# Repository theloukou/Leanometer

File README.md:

# Leanometer - IN DEVELOPMENT
ESP32-based motorcycle leanometer

This is version 2 of my open-source motorcycle leanometer, based on ESP32 SoM, programmed on Arduino.
Designed mainly to be compact, low cost, and easy to assemble with household equipment/average soldering skills.

3D printed enclosure has been tested to be water resistant over 12 hour water exposure. Additional weather proofing can be achieved by using some kind of conformal coating on electronics (i.e. Kontakt Plastik 70).

Additional parts needed are:
1.  **GY-521 MPU-6050** IMU module  ???
2. 26.5mm x 29mm x 3mm Plexiglass piece  ???
3. 6 pieces of M2.5x5mm bolts  ???
4. some kind of 2 component adhesive/thermoglue  ???

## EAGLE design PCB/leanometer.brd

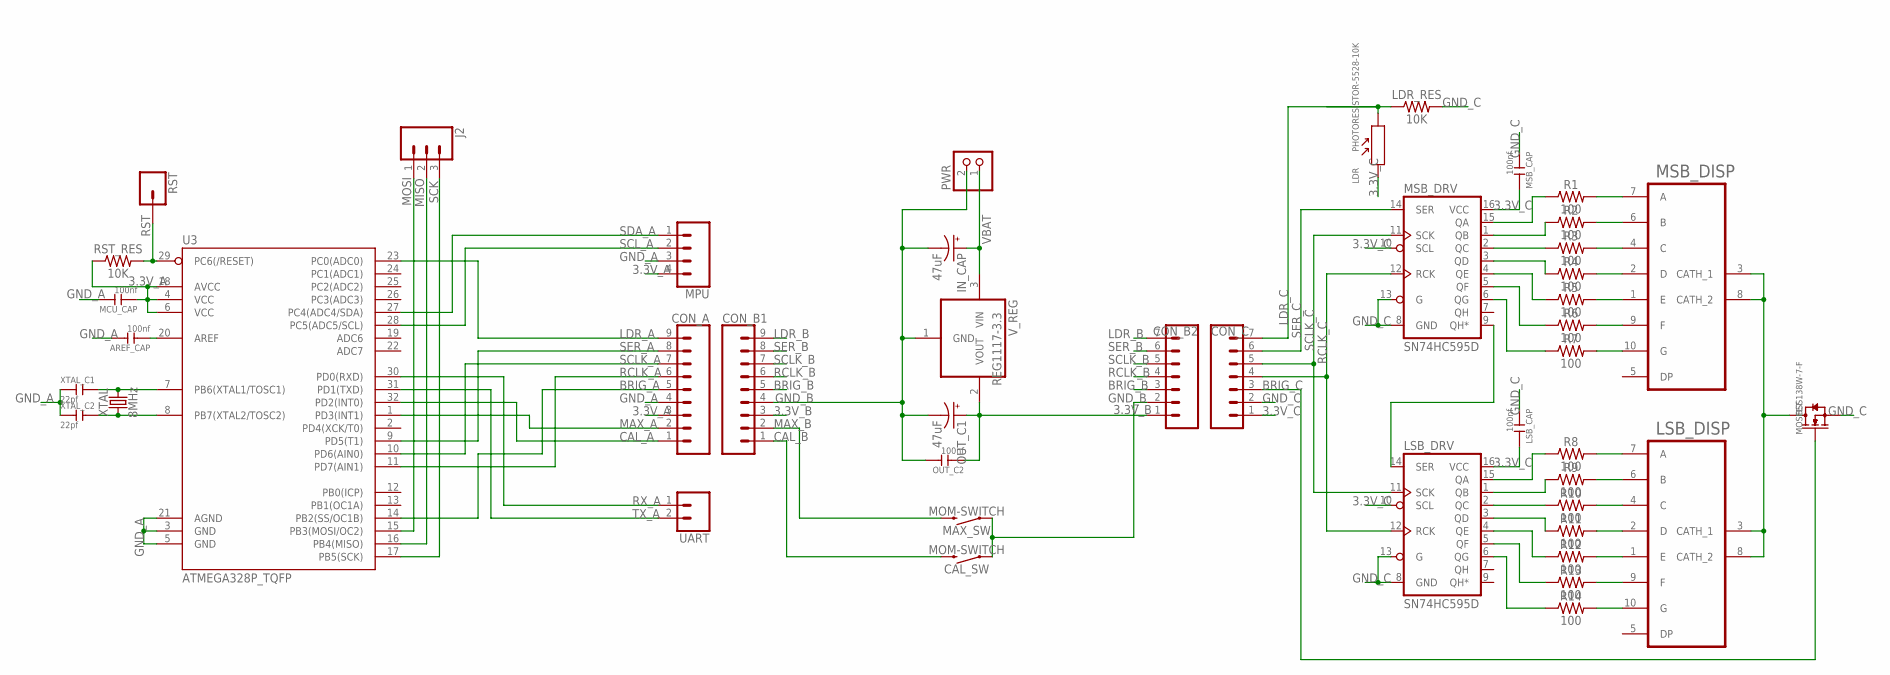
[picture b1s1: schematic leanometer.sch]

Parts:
AREF_CAP: 100nf; C0805
CAL_SW: MOM-SWITCH; TACTILE_SWITCH_PTH_6.0MM
CON_A: CONN_09; 1X09
CON_B1: CONN_09; 1X09
CON_B2: CONN_07; 1X07
CON_C: CONN_07; 1X07
IN_CAP: 47uF; CPOL-RADIAL-2.5MM-6.5MM
J2: CONN_03; 1X03
LDR: PHOTORESISTOR-5528-10K; SNR2-3.0
LDR_RES: 10K; 0805
LSB_CAP: 100nf; C0805
LSB_DISP: OPD-S5621LE-BW; 0.56''_LED_DISPLAY
LSB_DRV: SN74HC595D; SO16
MAX_SW: MOM-SWITCH; TACTILE_SWITCH_PTH_6.0MM
MCU_CAP: 100nf; C0805
MOSFET: BSS138W-7-F; SOT-23
MPU: CONN_04; 1X04
MSB_CAP: 100nf; C0805
MSB_DISP: OPD-S5621LE-BW; 0.56''_LED_DISPLAY
MSB_DRV: SN74HC595D; SO16
OUT_C1: 47uF; CPOL-RADIAL-2.5MM-6.5MM
OUT_C2: 100nf; C0805
PWR: JST_2PIN-THM-RA; JST-PH-2-THM-RA
R1, R2, R3, R4, R5, R6, R7, R8, R9, R10, R11, R12, R13, R14: 100; 0805
RST: CONN_01; 1X01
RST_RES: 10K; 0805
U3: ATMEGA328P_TQFP; TQFP32-08
UART: CONN_02; 1X02
V_REG: REG1117-3.3; SOT223
XTAL: 8MHz; HC49US
XTAL_C1, XTAL_C2: 22pf; C0805

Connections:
3.3V_A: CON_A.3, MCU_CAP.1, MPU.4, RST_RES.1, U3.4 (VCC), U3.6 (VCC), U3.18 (AVCC)
3.3V_B: CON_B1.3, CON_B2.1, OUT_C1.1 (+), OUT_C2.1, V_REG.2 (VOUT)
3.3V_C: CON_C.1, LDR.1, LSB_CAP.2, LSB_DRV.10 (SCL), LSB_DRV.16 (VCC), MSB_CAP.2, MSB_DRV.10 (SCL), MSB_DRV.16 (VCC)
BRIG_A: CON_A.5, U3.14 (PB2(SS/OC1B))
BRIG_B: CON_B1.5, CON_B2.3
BRIG_C: CON_C.3, MOSFET.1 (G)
CAL_A: CON_A.1, U3.32 (PD2(INT0))
CAL_B: CAL_SW.3 (2), CON_B1.1
GND_A: AREF_CAP.2, CON_A.4, MCU_CAP.2, MPU.3, U3.3 (GND), U3.5 (GND), U3.21 (AGND), XTAL_C1.1, XTAL_C2.1
GND_B: CAL_SW.1, CON_B1.4, CON_B2.2, IN_CAP.2 (-), MAX_SW.1, OUT_C1.2 (-), OUT_C2.2, PWR.2 (1), V_REG.1 (GND)
GND_C: CON_C.2, LDR_RES.2, LSB_CAP.1, LSB_DRV.8 (GND), LSB_DRV.13 (G), MOSFET.2 (S), MSB_CAP.1, MSB_DRV.8 (GND), MSB_DRV.13 (G)
LDR_A: CON_A.9, U3.23 (PC0(ADC0))
LDR_B: CON_B1.9, CON_B2.7
LDR_C: CON_C.7, LDR.2, LDR_RES.1
MAX_A: CON_A.2, U3.1 (PD3(INT1))
MAX_B: CON_B1.2, MAX_SW.3 (2)
MISO: J2.2, U3.16 (PB4(MISO))
MOSI: J2.1, U3.15 (PB3(MOSI/OC2))
unnamed: MSB_DISP.7 (A), R1.2
unnamed: MSB_DISP.6 (B), R2.2
unnamed: MSB_DISP.4 (C), R3.2
unnamed: MSB_DISP.2 (D), R4.2
unnamed: MSB_DISP.1 (E), R5.2
unnamed: MSB_DISP.9 (F), R6.2
unnamed: MSB_DISP.10 (G), R7.2
unnamed: LSB_DISP.7 (A), R8.2
unnamed: LSB_DISP.6 (B), R9.2
unnamed: LSB_DISP.4 (C), R10.2
unnamed: LSB_DISP.2 (D), R11.2
unnamed: LSB_DISP.1 (E), R12.2
unnamed: LSB_DISP.9 (F), R13.2
unnamed: LSB_DISP.10 (G), R14.2
unnamed: MSB_DRV.1 (QB), R2.1
unnamed: LSB_DRV.1 (QB), R9.1
unnamed: MSB_DRV.2 (QC), R3.1
unnamed: MSB_DRV.3 (QD), R4.1
unnamed: MSB_DRV.4 (QE), R5.1
unnamed: MSB_DRV.5 (QF), R6.1
unnamed: MSB_DRV.6 (QG), R7.1
unnamed: MSB_DRV.15 (QA), R1.1
unnamed: LSB_DRV.15 (QA), R8.1
unnamed: LSB_DRV.2 (QC), R10.1
unnamed: LSB_DRV.3 (QD), R11.1
unnamed: LSB_DRV.4 (QE), R12.1
unnamed: LSB_DRV.5 (QF), R13.1
unnamed: LSB_DRV.6 (QG), R14.1
unnamed: LSB_DRV.14 (SER), MSB_DRV.9 (QH*)
unnamed: LSB_DISP.3 (CATH_1), LSB_DISP.8 (CATH_2), MOSFET.3 (D), MSB_DISP.3 (CATH_1), MSB_DISP.8 (CATH_2)
unnamed: U3.7 (PB6(XTAL1/TOSC1)), XTAL.2, XTAL_C1.2
unnamed: U3.8 (PB7(XTAL2/TOSC2)), XTAL.1, XTAL_C2.2
unnamed: AREF_CAP.1, U3.20 (AREF)
RCLK_A: CON_A.6, U3.11 (PD7(AIN1))
RCLK_B: CON_B1.6, CON_B2.4
RCLK_C: CON_C.4, LSB_DRV.12 (RCK), MSB_DRV.12 (RCK)
RST: RST.1, RST_RES.2, U3.29 (PC6(/RESET))
RX_A: U3.30 (PD0(RXD)), UART.1
SCK: J2.3, U3.17 (PB5(SCK))
SCLK_A: CON_A.7, U3.10 (PD6(AIN0))
SCLK_B: CON_B1.7, CON_B2.5
SCLK_C: CON_C.5, LSB_DRV.11 (SCK), MSB_DRV.11 (SCK)
SCL_A: MPU.2, U3.28 (PC5(ADC5/SCL))
SDA_A: MPU.1, U3.27 (PC4(ADC4/SDA))
SER_A: CON_A.8, U3.9 (PD5(T1))
SER_B: CON_B1.8, CON_B2.6
SER_C: CON_C.6, MSB_DRV.14 (SER)
TX_A: U3.31 (PD1(TXD)), UART.2
VBAT: IN_CAP.1 (+), PWR.1 (2), V_REG.3 (VIN)

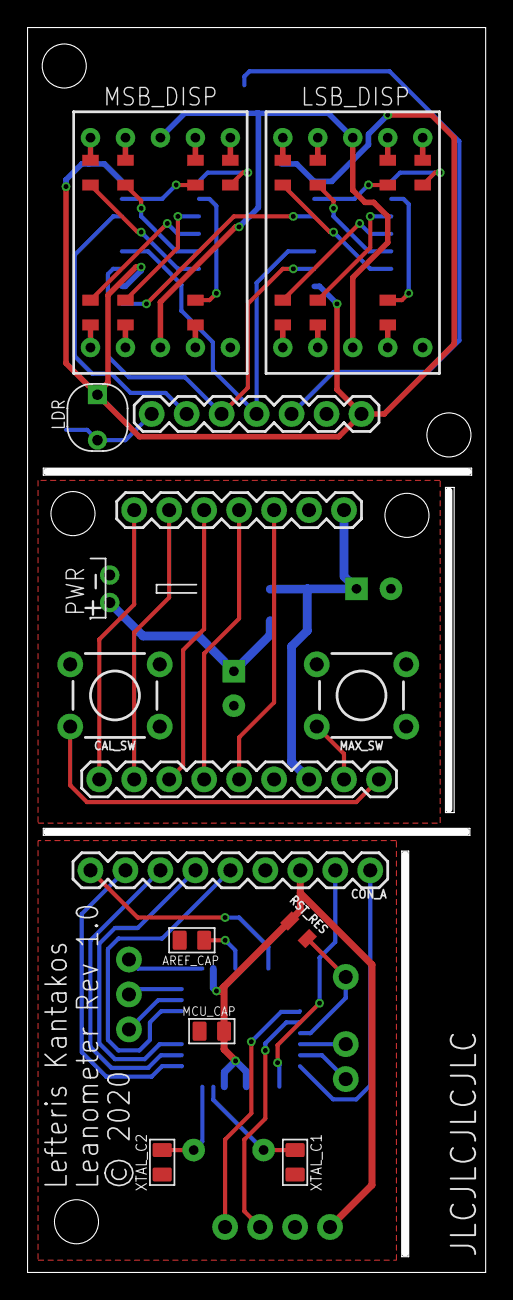
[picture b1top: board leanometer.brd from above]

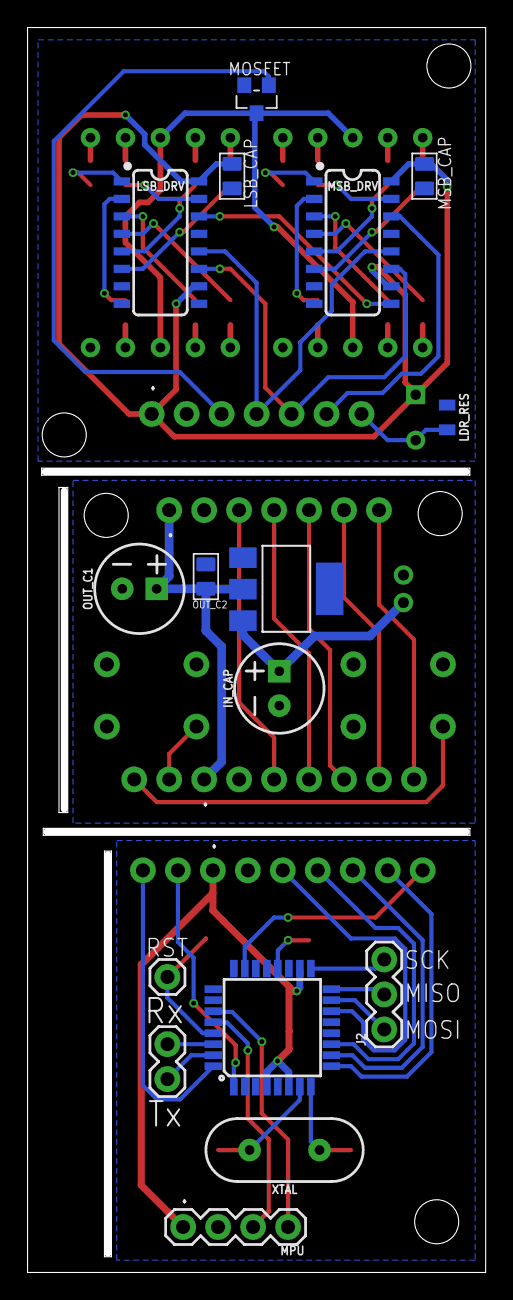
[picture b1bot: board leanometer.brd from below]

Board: 2 copper layers, 32.8 x 89.9 mm, 45 parts (16 on the bottom side), 67 nets.

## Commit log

2020-08-15 Changed to 3.3Volt power/logic
    Communication between MCU and MPU was stoppping due to difference between logic levels, and highly noisy environment of motorcycle.
    Change to all 3.3Volt makes the system much more resilient.
2023-03-10 1st commit
2023-03-15 Changed pin defs, swapped EEPROM for Preferences, added initial SD support

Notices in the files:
PCB/leanometer.brd:
© 2020
parts and their libraries:
SparkFun-Switches: Licensing: Creative Commons ShareAlike 4.0 International - https://creativecommons.org/licenses/by-sa/4.0
